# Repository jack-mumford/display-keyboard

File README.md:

# Display Keyboard

This project is the hardware design and software for a USB keyboard with an
integrated touch display.

Hardware features:

* Mechanical keys.
* [FeatherS2](https://unexpectedmaker.com/shop/feathers2-esp32-s2). This is a
  [ESP32-S2](https://www.espressif.com/sites/default/files/documentation/esp32-s2_datasheet_en.pdf)
  based embedded development board.
* 2.8" LCD capacitive [touch display](https://www.adafruit.com/product/2770).
* 0.91" vertical [OLED display](https://www.aliexpress.com/item/32672229793.html)
  for volume display.
* Volume control knob.

The FeatherS2 conforms to the [Adafruit Feather](https://www.adafruit.com/feather)
requirements, and allows for the possibility of replacing that MCU with another
Feather with little (if any) PCB rework.

## Hardware Design

Design is done in [KiCad](https://kicad.org/). Files are located in
the [pcb](pcb) directory.

## Software Requirements

* [ESP-IDF](https://docs.espressif.com/)
* [VS Code extensions](https://docs.espressif.com/projects/esp-idf/en/latest/esp32/get-started/vscode-setup.html)
  (optional)

## Getting Code

```sh
git clone https://github.com/jack-mumford/display-keyboard.git
cd display-keyboard
./make submodules
```

**Note**: This project makes use of new features (USB) of the ESP32-S2
          and requires ESP-IDF v4.3.

## Building

Do this after opening a new terminal window:

```sh
. $HOME/esp/esp-idf/export.sh
```

Build and flash to the attached ESP32-S2 device as so:

```sh
./make flash
```

Configuration (GPIO pins, etc.) is stored in the sdkconfig.defaults file. This can
be changed using menuconfig as so:

```sh
./make config
```

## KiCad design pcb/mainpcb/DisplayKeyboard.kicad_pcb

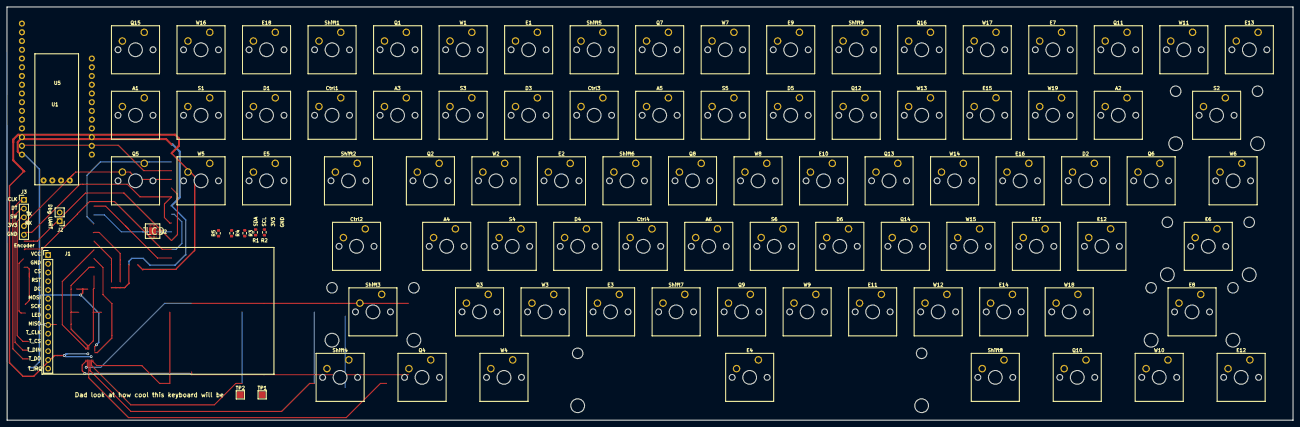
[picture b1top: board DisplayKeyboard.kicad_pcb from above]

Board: 2 copper layers, 373.9 x 120.1 mm, 98 parts (0 on the bottom side), 31 nets.

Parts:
A1: Delete/End; SW_Cherry_MX_1.00u_PCB
A2: = +; SW_Cherry_MX_1.00u_PCB
A3: 1 !; SW_Cherry_MX_1.00u_PCB
A4: A; SW_Cherry_MX_1.00u_PCB
A5: 5 %; SW_Cherry_MX_1.00u_PCB
A6: G; SW_Cherry_MX_1.00u_PCB
Ctrl1: `; SW_Cherry_MX_1.00u_PCB
Ctrl2: Caps; SW_Cherry_MX_1.75u_PCB
Ctrl3: 4 $; SW_Cherry_MX_1.00u_PCB
Ctrl4: F; SW_Cherry_MX_1.00u_PCB
D1: Page Down; SW_Cherry_MX_1.00u_PCB
D2: [ {; SW_Cherry_MX_1.00u_PCB
D3: 3 #; SW_Cherry_MX_1.00u_PCB
D4: D; SW_Cherry_MX_1.00u_PCB
D5: 7 &; SW_Cherry_MX_1.00u_PCB
D6: J; SW_Cherry_MX_1.00u_PCB
E1: F3; SW_Cherry_MX_1.00u_PCB
E2: E; SW_Cherry_MX_1.00u_PCB
E3: C; SW_Cherry_MX_1.00u_PCB
E4: Space; SW_Cherry_MX_6.25u_PCB
E5: RIGHT; SW_Cherry_MX_1.00u_PCB
E6: Enter; SW_Cherry_MX_2.25u_PCB
E7: F11; SW_Cherry_MX_1.00u_PCB
E8: Right Shift; SW_Cherry_MX_2.75u_PCB
E9: F7; SW_Cherry_MX_1.00u_PCB
E10: U; SW_Cherry_MX_1.00u_PCB
E11: M; SW_Cherry_MX_1.00u_PCB
E12: Right Control; SW_Cherry_MX_1.25u_PCB
E12#2: " '; SW_Cherry_MX_1.00u_PCB
E13: Num Lock; SW_Cherry_MX_1.00u_PCB
E14: . >; SW_Cherry_MX_1.00u_PCB
E15: 0 ); SW_Cherry_MX_1.00u_PCB
E16: P; SW_Cherry_MX_1.00u_PCB
E17: ; :; SW_Cherry_MX_1.00u_PCB
E18: Page UP; SW_Cherry_MX_1.00u_PCB
J1: Conn_01x14_Female; PinHeader_1x14_P2.54mm_Vertical
J2: UART Debug header; PinHeader_1x02_P2.54mm_Vertical
J3: Conn_01x05_Female; PinHeader_1x05_P2.54mm_Vertical
Q1: F1; SW_Cherry_MX_1.00u_PCB
Q2: Q; SW_Cherry_MX_1.00u_PCB
Q3: Z; SW_Cherry_MX_1.00u_PCB
Q4, Q10: Windows; SW_Cherry_MX_1.25u_PCB
Q5: LEFT; SW_Cherry_MX_1.00u_PCB
Q6: ] }; SW_Cherry_MX_1.00u_PCB
Q7: F5; SW_Cherry_MX_1.00u_PCB
Q8: T; SW_Cherry_MX_1.00u_PCB
Q9: B; SW_Cherry_MX_1.00u_PCB
Q11: F12; SW_Cherry_MX_1.00u_PCB
Q12: 8 *; SW_Cherry_MX_1.00u_PCB
Q13: I; SW_Cherry_MX_1.00u_PCB
Q14: K; SW_Cherry_MX_1.00u_PCB
Q15: Home/Pause; SW_Cherry_MX_1.00u_PCB
Q16: F9; SW_Cherry_MX_1.00u_PCB
R1, R2, R3, R4, R5: 2.2kΩ; R_0603_1608Metric
S1: UP; SW_Cherry_MX_1.00u_PCB
S2: Delete; SW_Cherry_MX_2.00u_PCB
S3: 2 @; SW_Cherry_MX_1.00u_PCB
S4: S; SW_Cherry_MX_1.00u_PCB
S5: 6 ^; SW_Cherry_MX_1.00u_PCB
S6: H; SW_Cherry_MX_1.00u_PCB
Shift1: Escape; SW_Cherry_MX_1.00u_PCB
Shift2: Tab; SW_Cherry_MX_1.50u_PCB
Shift3: Left Shift; SW_Cherry_MX_2.25u_PCB
Shift4: Control; SW_Cherry_MX_1.25u_PCB
Shift5: F4; SW_Cherry_MX_1.00u_PCB
Shift6: R; SW_Cherry_MX_1.00u_PCB
Shift7: V; SW_Cherry_MX_1.00u_PCB
Shift8: Right Alt; SW_Cherry_MX_1.25u_PCB
Shift9: F8; SW_Cherry_MX_1.00u_PCB
TP1, TP2: TestPoint; TestPoint_Pad_2.0x2.0mm
U1: 128x32_OLED_LCD_LED
U2: ADP5589
U5: FeatherS2
W1: F2; SW_Cherry_MX_1.00u_PCB
W2: W; SW_Cherry_MX_1.00u_PCB
W3: X; SW_Cherry_MX_1.00u_PCB
W4: Left Alt; SW_Cherry_MX_1.25u_PCB
W5: DOWN; SW_Cherry_MX_1.00u_PCB
W6: \ |; SW_Cherry_MX_1.50u_PCB
W7: F6; SW_Cherry_MX_1.00u_PCB
W8: Y; SW_Cherry_MX_1.00u_PCB
W9: N; SW_Cherry_MX_1.00u_PCB
W10: FN; SW_Cherry_MX_1.25u_PCB
W11: Print Screen; SW_Cherry_MX_1.00u_PCB
W12: , <; SW_Cherry_MX_1.00u_PCB
W13: 9 (; SW_Cherry_MX_1.00u_PCB
W14: O; SW_Cherry_MX_1.00u_PCB
W15: L; SW_Cherry_MX_1.00u_PCB
W16: Insert/Delete; SW_Cherry_MX_1.00u_PCB
W17: F10; SW_Cherry_MX_1.00u_PCB
W18: / ?; SW_Cherry_MX_1.00u_PCB
W19: - _; SW_Cherry_MX_1.00u_PCB

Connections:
3V3: J1.1, J1.8, J3.4, R1.2, R2.2, R3.2, R4.2, R5.2, U1.3, U2.18, U5.2
/Sheet60C95FD9/COL1: A3.2, A4.2, Q1.2, Q2.2, Q3.2, Q4.2, S1.2, S2.2
/Sheet60C95FD9/COL2: A1.1, A2.1, A5.2, A6.2, Ctrl3.2, Ctrl4.2, D1.1, D1.2, D2.1, D2.2, D3.2, D4.2, E1.2, E2.2, E3.2, E4.1, E4.2, E5.1, E5.2, E6.1, E6.2, E7.1, E7.2, E8.1, E8.2, E12.1, E12#2.1, E13.1, E13.2, E14.2, E18.1, Q4.1, Q5.1, Q5.2, Q6.1, Q6.2, Q7.2, Q8.2, Q9.2, Q10.1, Q10.2, Q11.1, Q12.2, Q13.2, Q14.2, Q15.1, Q15.2, Q16.2, S1.1, S2.1, S3.2, S4.2, S5.2, S6.2, Shift4.1, Shift5.2, Shift6.2, Shift7.2, Shift8.1, Shift8.2, Shift9.2, W1.2, W2.2, W3.2, W4.1, W4.2, W5.1, W5.2, W6.1, W6.2, W7.2, W8.2, W9.2, W10.1, W10.2, W11.1, W12.2, W13.2, W14.2, W15.2, W16.1, W16.2, W19.1
/Sheet60C95FD9/COL7: D5.2, D6.2, E9.2, E10.2, E11.2, E12.2, E12#2.2, Q11.2
/Sheet60C95FD9/COL10: E15.2, E16.2, E17.2, E18.2, W17.2, W18.2, W19.2
/Sheet60C95FD9/ROW0: E1.1, E9.1, Q1.1, Q7.1, Q16.1, Shift1.1, Shift5.1, Shift9.1, W1.1, W7.1, W17.1
/Sheet60C95FD9/ROW1: A3.1, A5.1, Ctrl1.1, Ctrl3.1, D3.1, D5.1, E15.1, Q12.1, S3.1, S5.1, W13.1
/Sheet60C95FD9/ROW2: E2.1, E10.1, E16.1, Q2.1, Q8.1, Q13.1, Shift2.1, Shift6.1, W2.1, W8.1, W14.1
/Sheet60C95FD9/ROW3: A4.1, A6.1, Ctrl2.1, Ctrl4.1, D4.1, D6.1, E17.1, Q14.1, S4.1, S6.1, W15.1
/Sheet60C95FD9/ROW4: E3.1, E11.1, E14.1, Q3.1, Q9.1, Shift3.1, Shift7.1, W3.1, W9.1, W12.1, W18.1
COL0: A1.2, A2.2, Ctrl1.2, Ctrl2.2, Shift1.2, Shift2.2, Shift3.2, Shift4.2, U2.9
D_CS: J1.3, U5.23
D_DC: J1.5, U5.10
Enc_CLK: J3.1, U5.9
Enc_DT: J3.2, U5.8
Enc_SW: J3.3, U5.7
GND: J1.2, J3.5, U1.4, U2.EP, U5.4
I2C0_SCL: R4.1, TP2.1, U2.23, U5.18
I2C0_SDA: R3.1, TP1.1, U2.22, U5.17
I2C1_SCL: R2.1, U1.2, U5.22
I2C1_SDA: R1.1, U1.1, U5.21
KBD_INT: R5.1, U2.24, U5.20
KBD_RST: U2.17, U5.19
MISO: J1.9, J1.13, U5.13
MOSI: J1.6, J1.12, U5.12
unnamed: J2.1, U5.15
unnamed: J2.2, U5.14
RST: J1.4, U5.1
SCK: J1.7, J1.10, U5.11
T_CS: J1.11, U5.24
T_IRQ: J1.14, U5.25

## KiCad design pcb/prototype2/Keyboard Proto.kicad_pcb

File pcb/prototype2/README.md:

The prototype board is to validate the proper use of the
[TCA8418](https://www.ti.com/lit/ds/symlink/tca8418.pdf) keyboard IC.

There are a few errors in this first prototype board:

1. The through holes for the MCU were too small. Fortunately the MCU
   board could be squeezed in (just barely). The LCD holes were the
   correct diameter.
2. The LCD screen was too close to the top row of buttons. The goal
   was to have two rows of mechanical switches (Cherry MX), but
   fortunately there was (just barely) enough space for tactile
   switches.
3. Unused [TCA8418](https://www.ti.com/lit/ds/symlink/tca8418.pdf) key switches
   should have been tied to VCC (via resistors).

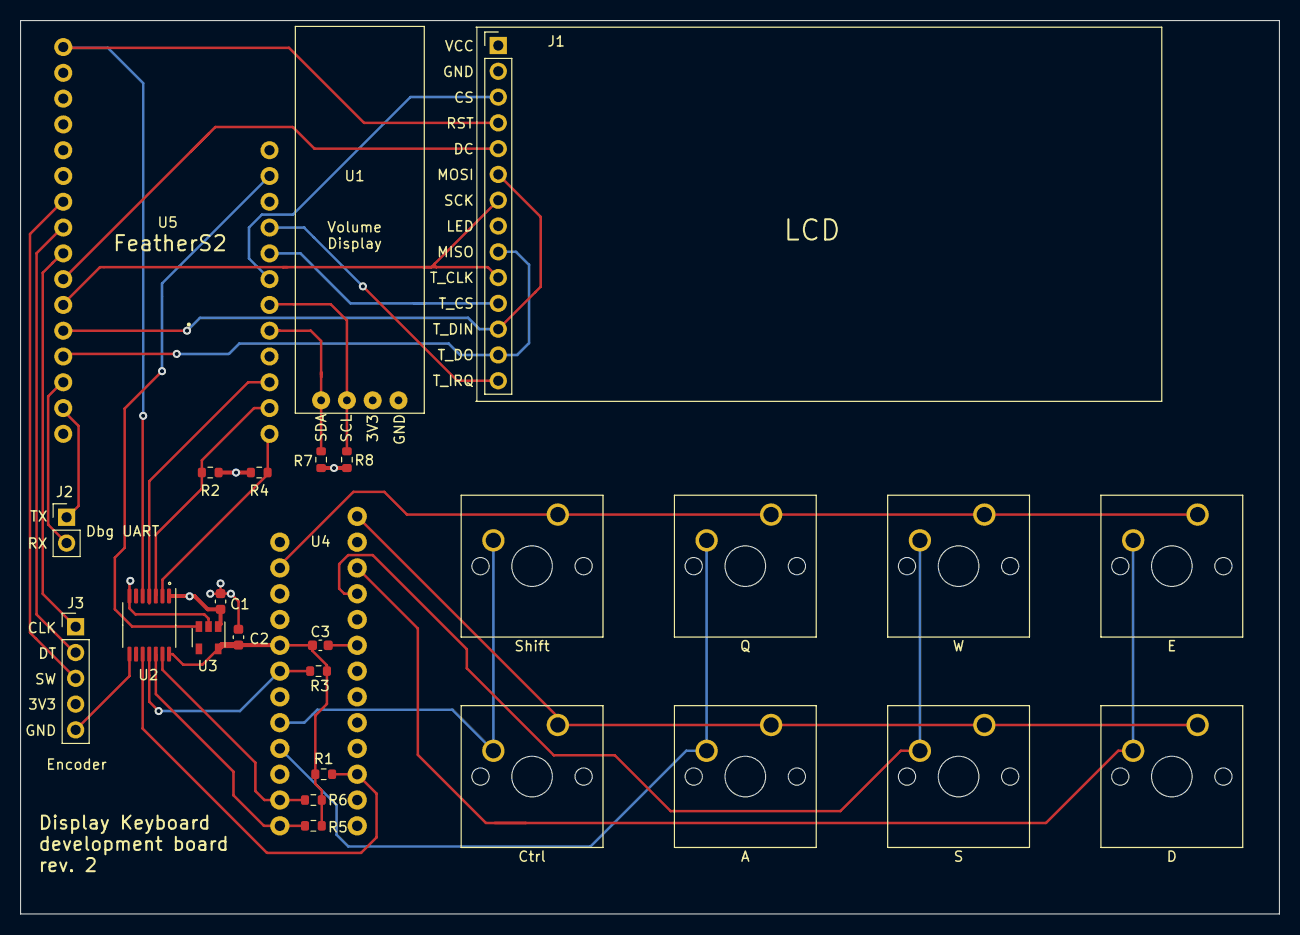
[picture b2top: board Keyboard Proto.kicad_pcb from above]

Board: 4 copper layers, 124.0 x 88.0 mm, 27 parts (0 on the bottom side), 32 nets.

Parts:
A1: A; SW_Cherry_MX_1.00u_PCB
C1, C2: 1µF/10V; C_0603_1608Metric
C3: 0.1μF; C_0603_1608Metric
Ctrl1: Ctrl; SW_Cherry_MX_1.00u_PCB
D1: D; SW_Cherry_MX_1.00u_PCB
E1: E; SW_Cherry_MX_1.00u_PCB
J1: Conn_01x14_Female; PinHeader_1x14_P2.54mm_Vertical
J2: UART Debug header; PinHeader_1x02_P2.54mm_Vertical
J3: Conn_01x05_Female; PinHeader_1x05_P2.54mm_Vertical
Q1: Q; SW_Cherry_MX_1.00u_PCB
R1, R3, R5, R6: 106Ω; R_0603_1608Metric
R2, R4, R7, R8: 5kΩ; R_0603_1608Metric
S1: S; SW_Cherry_MX_1.00u_PCB
Shift1: Shift; SW_Cherry_MX_1.00u_PCB
U1: 128x32_OLED_LCD_LED
U2: LSF0204DPWR; TSSOP-14_4.4x5mm_P0.65mm
U3: MIC5504-1.8YM5; SOT-23-5
U4: LM8330; BGA0016
U5: FeatherS2
W1: W; SW_Cherry_MX_1.00u_PCB

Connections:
1V8: C2.1, C3.2, R1.2, R3.2, R5.2, R6.2, U2.14, U3.5, U4.D3
1V8_KBDINT: R3.1, U2.11, U4.C5
1V8_RST: R1.1, U2.10, U4.A3
1V8_SCL: R5.1, U2.12, U4.A4
1V8_SDA: R6.1, U2.13, U4.A5
3V3: C1.1, J1.1, J1.8, J3.4, R2.2, R4.2, R7.2, R8.2, U1.3, U2.1, U3.1, U5.2
3V3_KBDINT: U2.4, U5.19
3V3_RST: J1.4, U2.5, U5.1
3V3_SCL: R2.1, U2.3, U5.18
3V3_SDA: R4.1, U2.2, U5.17
COL0: D1.2, E1.2, U4.E1
COL1: S1.2, U4.D2, W1.2
COL2: A1.2, Q1.2, U4.B4
COL3: Ctrl1.2, Shift1.2, U4.B5
D_CS: J1.3, U5.23
D_DC: J1.5, U5.10
EN: U3.3, U5.27
Enc_CLK: J3.1, U5.9
Enc_DT: J3.2, U5.8
Enc_SW: J3.3, U5.7
GND: C1.2, C2.2, C3.1, J1.2, J3.5, U1.4, U2.7, U2.8, U3.2, U4.C3, U5.4
MISO: J1.9, J1.13, U5.13
MOSI: J1.6, J1.12, U5.12
unnamed: J2.1, U5.15
unnamed: J2.2, U5.14
ROW0: E1.1, Q1.1, Shift1.1, U4.E4, W1.1
ROW1: A1.1, Ctrl1.1, D1.1, S1.1, U4.E3
SCK: J1.7, J1.10, U5.11
SCL: R8.1, U1.2, U5.22
SDA: R7.1, U1.1, U5.21
T_CS: J1.11, U5.24
T_IRQ: J1.14, U5.25

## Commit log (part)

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2021-01-07 Changes for new ESP-IDF.
2021-01-07 Deleted TCA8418 code.
    It only supports 80 keys, so moving to the LM8330.
2021-01-07 LM8330: Initializing keyboard IC.
    As per datasheet table 4.
2021-01-08 LM8330: Updated comments.
2021-01-08 LM8330: Moved register definitions to own file.
2021-01-08 LM8330: More register structure definitions.
2021-01-08 ESP_IF_WIFI_STA → WIFI_IF_STA.
2021-01-08 TCA8418: AI=true, INT_CFG=false.
2021-01-08 Dispatching USB HID keyboard events.
2021-01-08 make.py: Fixed list/scalar bug.
2021-01-08 Set LED GPIO for FeatherS2.
2021-01-08 Yielding from ISR when posting events.
2021-01-08 TinyUSB: Lowered debug level.
2021-01-09 LVGL: Using dark theme.
2021-01-10 make: fixed typo.
2021-01-10 sdkconfig: local hostname "espressif" → "display-keyboard".
2021-01-10 sdkconfig: Enable HTTPS server by default.
2021-01-10 sdkconfig: Setting PSPRAM (and other RAM) values for FeatherS2.
    From:
    https://github.com/adafruit/circuitpython/ports/esp32s2/boards/unexpectedmaker_feathers2
2021-01-10 sdkconfig: Default to LVGL dark theme.
2021-01-10 sdkconfig: Integrated SPIRAM into the heap.
    Made the two following changes:
    ESP32S2-specific/
    SPI RAM config/
    SPI RAM access method/
    (*) Make RAM allocatable using malloc() as well
    (*) Try to allocate memories of WiFi and LWIP in SPIRAM firstly.
2021-01-10 make.py: Tolerating missing sdkconfig file.
2021-01-11 Added drawing of test image.
2021-01-23 make: Using pySerial.
2021-01-25 Switched LM8330 to BGA0016 footprint.
2021-01-26 PCB changes for LM8330 breakout.
2021-01-26 Relayout most of PCB for Feather S2 symbol fix.
2021-01-27 proto r2: Relayout complete.
2021-01-27 proto r2: Tweaked silkscreen and removed unneeded vias.
2021-02-07 Added dot for LSF0204DPWR pin 1.
2021-02-08 Added volume display.
    Not yet working because LVGL is currently only configured to talk
    to one type of display.
2021-02-08 Back to UNIX style EOL for make.py.
    Using Windows EOL's breaks the shebang use of the script.
2021-02-11 Updated *all* components to tip-of-tree.
2021-02-11 Updated sdkconfig for LVGL tip-of-tree.
2021-02-12 Some work on multiple screens.
    Not yet working.
2021-02-13 Added GitHub workflow to check against .editorconfig.
2021-02-13 Ignoring KiCad in .editorconfig.
    KiCad doesn't add a trailing LF to the file.
    Also, skipping C++ indent. Clang-format produces a format that
    .editorconfig finds problematic.
2021-02-13 README: setting working directory during checkout.
2021-02-13 SSD1306: Added set_px_cb to actually draw.
2021-02-13 Start of canvas code.
    Appears to be a LVGL bug. Need to debug.
2021-02-13 Volume display is working!
2021-02-13 CONFIG_LV_VER_RES_MAX=320.
2021-02-13 CMakeLists.txt: removed quotes.
2021-02-13 Minor improvements to spotify display.
2021-02-13 Created VolumeWidget.
2021-02-13 Setting VolumeWidget to square.
2021-02-14 Moved all UI to own task.
2021-02-14 Misc cleanup.
2021-02-18 Moved allocation from App::Initialize to constructor.
2021-02-19 Config is inline member.
2021-02-19 https_server is inline member.
2021-02-19 Created MainTask.
2021-02-20 Relaying WiFi status to UI.
2021-02-20 Added MainScreen::Initialize.
2021-02-20 Converted logging TAGs to mixed case.
2021-02-20 Remove early initialization of main screen.
2021-02-20 UITask: Made displays members.
2021-02-20 Removed MainDisplay::HandleTask().
2021-02-20 Not waiting for debug monitor on Feather S2.
2021-02-20 MainDisplay no longer given size.
2021-02-21 proto r2: Added current schematic/layout PDF's
2021-02-21 proto r2: Connected LSF0204D EN pin to GND.
    The LSF0204D's EN pin should be pulled low to disable. The
    design was correct for the "non-D" version of the chip.
2021-02-21 Added (fixed) WiFi status bar icon.
2021-02-21 Cleaned up I2C constants.
2021-02-21 Updated components/lv_port_esp32.
2021-02-24 Added 0.1μF Cap to LM8330 VCC.
2021-02-26 Added tarablessd1306 submodule.
2021-02-27 Deleted DRAW_VOLUME_DISPLAY constant.
2021-02-27 Clearing bits when reading events.
2021-02-27 Inverted volume display and contrast test.
2021-02-27 Removed unused HID::Initialize.
2021-02-27 Fixed components/tarablessd1306 in makefile.
2021-02-27 Disabled keyboard simulator.
2021-02-27 Sped up volume simulator loop.
2021-02-27 Created VolumeTask.
2021-02-27 VolumeDisplay: Removed disused constants.
2021-02-28 Renamed all Keyboard Proto files to Display Keyboard
2021-02-28 Added a time status bar item.
2021-02-28 Fixed a few dangling references to proto2.
2021-02-28 Added gear icon to status bar.
2021-02-28 Added Spotify status bar icon.
2021-02-28 Added large Spotify logo.
2021-03-01 Setting dark mode.
2021-03-01 Enabled LVGL touch panel.
2021-03-03 Submodule changes: -lv_port_esp32, +lvgl, +lvgl_esp32_drivers.
2021-03-06 sdkconfig cleaning.
2021-03-06 MainDisplay owns touch panel.
2021-03-06 MainScreen cleanup.
2021-03-06 make: added app-flash target.
2021-03-06 Re-added display images.
    The prior LVGL memory fix fixes these.
2021-03-06 LVGL: Set TFT to full duplex 80 MHz.
2021-03-06 LM8330: Designated RESETN pin as active low.
2021-03-06 KeyCad => KiCad.
2021-03-07 Created AlbumArtDownloaderTask (but not starting).
2021-03-07 README: cleaned up build instructions.
2021-03-07 MainScreen: cosmetic improvements.
    1. Changed rating image pos.
    2. Changed album artwork size.
    3. Raised metadata.
2021-03-07 Switched back to tskIDLE_PRIORITY + 1.
2021-03-07 HTTP: Fixed use after free bug.
2021-03-07 Increased fetcher stack size.
2021-03-07 Fixed cover art URL.
2021-03-07 AlbumArtDownloaderTask → ResourceFetcher.
2021-03-08 Added All Keys to New Keyboard Matrix
2021-03-08 Switched to tarablessd1306 fork to eliminate warnings.
2021-03-08 Added memory display for debug.
2021-03-09 Converted static UI images to inline.
2021-03-11 More memory diagnostics.
2021-03-11 More IRAM savings.
2021-03-12 Added test to fetch test image every 5 sec.
2021-03-13 Deleted LVGLDrive.
    No longer reading images from the filesystem. They will either be
    hard-coded as static data, or fetched from the Internet.
2021-03-14 make: ensuring app-flash has a port.
2021-03-14 Switched to cmumford/TJpgDec.
    The authoritative [TJpgDec](http://elm-chan.org/fsw/tjpgd/00index.html)
    library, which is included unchanged in LVGL's https://github.com/lvgl/lv_lib_split_jpg,
    has memory bugs. Switching to cmumford/TJpgDec, which has some bug fixes
    in these areas, and more suitable for decoding JPEG's downloaded
    from the Internet.
2021-03-14 Start of image resize. Just getting TL corner for now.
2021-03-14 Reduced debug RAM display lines.
2021-03-15 Scaling image with nearest neighbor.
2021-03-15 HTTPClient: improved error checking.
2021-03-15 Treating empty fetched resource as error.
2021-03-15 Tweaked HTTP client status.
2021-03-15 Fetching test image every 12 sec.
2021-03-16 Set LV_IMG_CACHE_DEF_SIZE=0
2021-03-20 LM8330: Made RESETN pin active low.
2021-03-21 Using 10-bit keyboard I2C address (not working).
2021-03-21 Improved test cover art fetch.
2021-03-21 Deleted components/lv_lib_split_jpg.
    This should have been part of e632dcc6d614cb044d7f3f71c4e9fcbaf50b441a.
2021-03-21 Updated proto r2 readme.
2021-03-22 Moved tinyusb from comonents/ to libs/.
2021-03-23 Added KiCad files to Git ignore.
2021-03-24 proto3: Swapped 3.3V/1.8V on level shifter.
2021-03-24 proto3: Converted from 4 to 2 layers.
2021-03-26 New i2clib and mode/size changes as required by upstream change.
2021-03-26 Added APA102 control.
    This is the RGB LED onboard the Feather S2.
    Building with esp-idf@1067b28707e527f177752741e3aa08b5dc64a4d7
2021-03-27 tweaked flash-feathers2-stock-bootloader make target.
2021-03-27 APA102: It is more or less working.
    Outstanding issues:
    1. The RGB pixel values are supposed to be 8-bit values, but
    needed to scale down to 5-bit values to prevent wrapping
    values.
    2. Intensity is not yet correct.
2021-03-27 Including headers from IDF_PATH/components.
    Including headers consistent to how they are included in the
    ESP-IDF documentation. (i.e. <driver/include/driver/gpio.h>
    instead of <driver/gpio.h>).
    The ideal is to have only one include path in the cmake file:
    "${IDF_PATH}/components"
    however, some ESP-IDF headers include files w/o a path, so some
2021-03-28 Switched from C++11 to C++17.
2021-03-28 Added C++14 digit separators.
2021-03-28 Improved "fetching cover" debug message.
2021-03-28 Compiler options: CONFIG_COMPILER_STACK_CHECK_MODE_STRONG=y
2021-03-28 NewKeyMatrix
2021-03-28 Copied Keys from old pcb to New PCB
2021-03-28 Renamed Files
2021-03-28 Deleted old pcb
2021-03-30 Made clean target work on Windows.
    Not a great implementation, but it works.
2021-03-30 Fixed formatting.
2021-04-04 Default RGB led intensity is 255.
2021-04-04 Experimenting with resetting LM8330 at startup.
2021-04-07 Proto 3 schematic PDF.
2021-04-09 ADP5589 Keyboard IC symbol.
2021-04-09 Modified schematic for ADP5589.
2021-04-11 Relayout proto 4.
2021-04-16 ADP5589: Add register file.
2021-04-16 ADP5589: Add register structs up to 0x32.
2021-04-19 ADP5589: Completed register definition structs.
2021-05-09 Updated ADP5589 footprint.
    Also, first save with KiCAD 5.1.10.
2021-05-16 Made APA102::Color constexpr.
2021-05-16 MainTask::InitializeI2C now static.
2021-05-16 Fixed pin init 32-bit wrap bug.
2021-05-27 Some work on keyboard initialization.
2021-05-29 ADP5589: FIFO docs.
2021-05-29 Reading keyboard FIFO.
2021-05-29 make.bat: selecting device/serial ports.
2021-05-29 keyboard: Changed event interrupt to low level.
2021-05-29 keyboard: cleanup INT init code.
2021-05-29 Formatted make.py.
2021-05-30 More work on initializing ADP5589.
2021-05-30 Added 1-sec. keyboard FIFO logger.
2021-05-30 Keyboard: Fixed event count check.
2021-05-31 keyboard: receiving events.
    Receiving and logging keyboard events. They don't have the correct
    values yet, but making progress.
2021-05-31 ADP5589: tweaked comment.
2021-05-31 ADP5589: Added enums to header.
2021-06-01 ADP5589: Added more register structs.
2021-06-09 ADP5589: Script to generate key enum values.
2021-06-11 ADP5589 Fixed ADP5589 event ID enum.
    The values were simply incorrect.
2021-06-11 ADP5589: Fixed CoreFrequency constants: MHz → kHz.
2021-06-11 Fixed ADP5589 register IO.
    Was incorrectly relying on bitfields being in a specific
    order which was bad practice.
2021-06-11 Disable keyboard logging task.
2021-06-11 Updated i2clib => 41c0e1fc43163dd9b686ffb7ce2be01cec0260b5.
2021-06-12 Created Register namespace.
2021-06-13 Using array for keyboard config.
2021-06-14 Deleted earlier prototypes.
2021-06-14 Minor cleanup.
2021-06-14 docs cleanup.
2021-06-15 proto: KBDINT → KBD_INT.
2021-06-15 renamed make.bat → make.ps1.
2021-06-15 Added expicit for single param constructors.
2021-06-15 Deleted unused member: time_update_timer_.
2021-06-15 Converted std::vector to std::array.
2021-06-16 Fixed typo.
2021-06-19 Upgraded TJpgDec to R0.02a.
2021-06-20 Upgraded kbdlib.
2021-06-26 Switched from ADP5589 to LM8330 chip.
2021-06-29 Created Subsheet
2021-06-29 updated main pcb.
2021-07-06 Back to LM8330 based prototype (no. 3).
2021-07-06 Added prototype layout PDF.
2021-07-06 Improvements to keyboard initialization.
2021-07-06 Reading keyboard events reporting to HID.
2021-07-06 Re clang-formatted.
2021-07-07 Added KEYBOARD_POLLING.
2021-07-10 More LM8330 initialization.
2021-07-11 Initializing KBDIC.
2021-07-11 Reading MFGCODE/SWREV in single I2C operation.
2021-07-11 Writing RSTINTCLR=0x1 to release IRQN pin.
2021-07-18 Changes for i2clib refactoring.
2021-07-22 Cleaned up Keyboard::EnableInterrupts().
2021-07-23 Attempt to create CI workflow.
2021-07-23 Fix workflow indentation.
2021-07-24 Switched GitHub build action to espressif/esp-idf-ci-action.
    Building release v4.3.
2021-07-24 Building PR's in pull GitHub workflow.
2021-07-24 Changed required ESP-IDF to v4.3.
2022-10-16 upgraded to kicad v6
